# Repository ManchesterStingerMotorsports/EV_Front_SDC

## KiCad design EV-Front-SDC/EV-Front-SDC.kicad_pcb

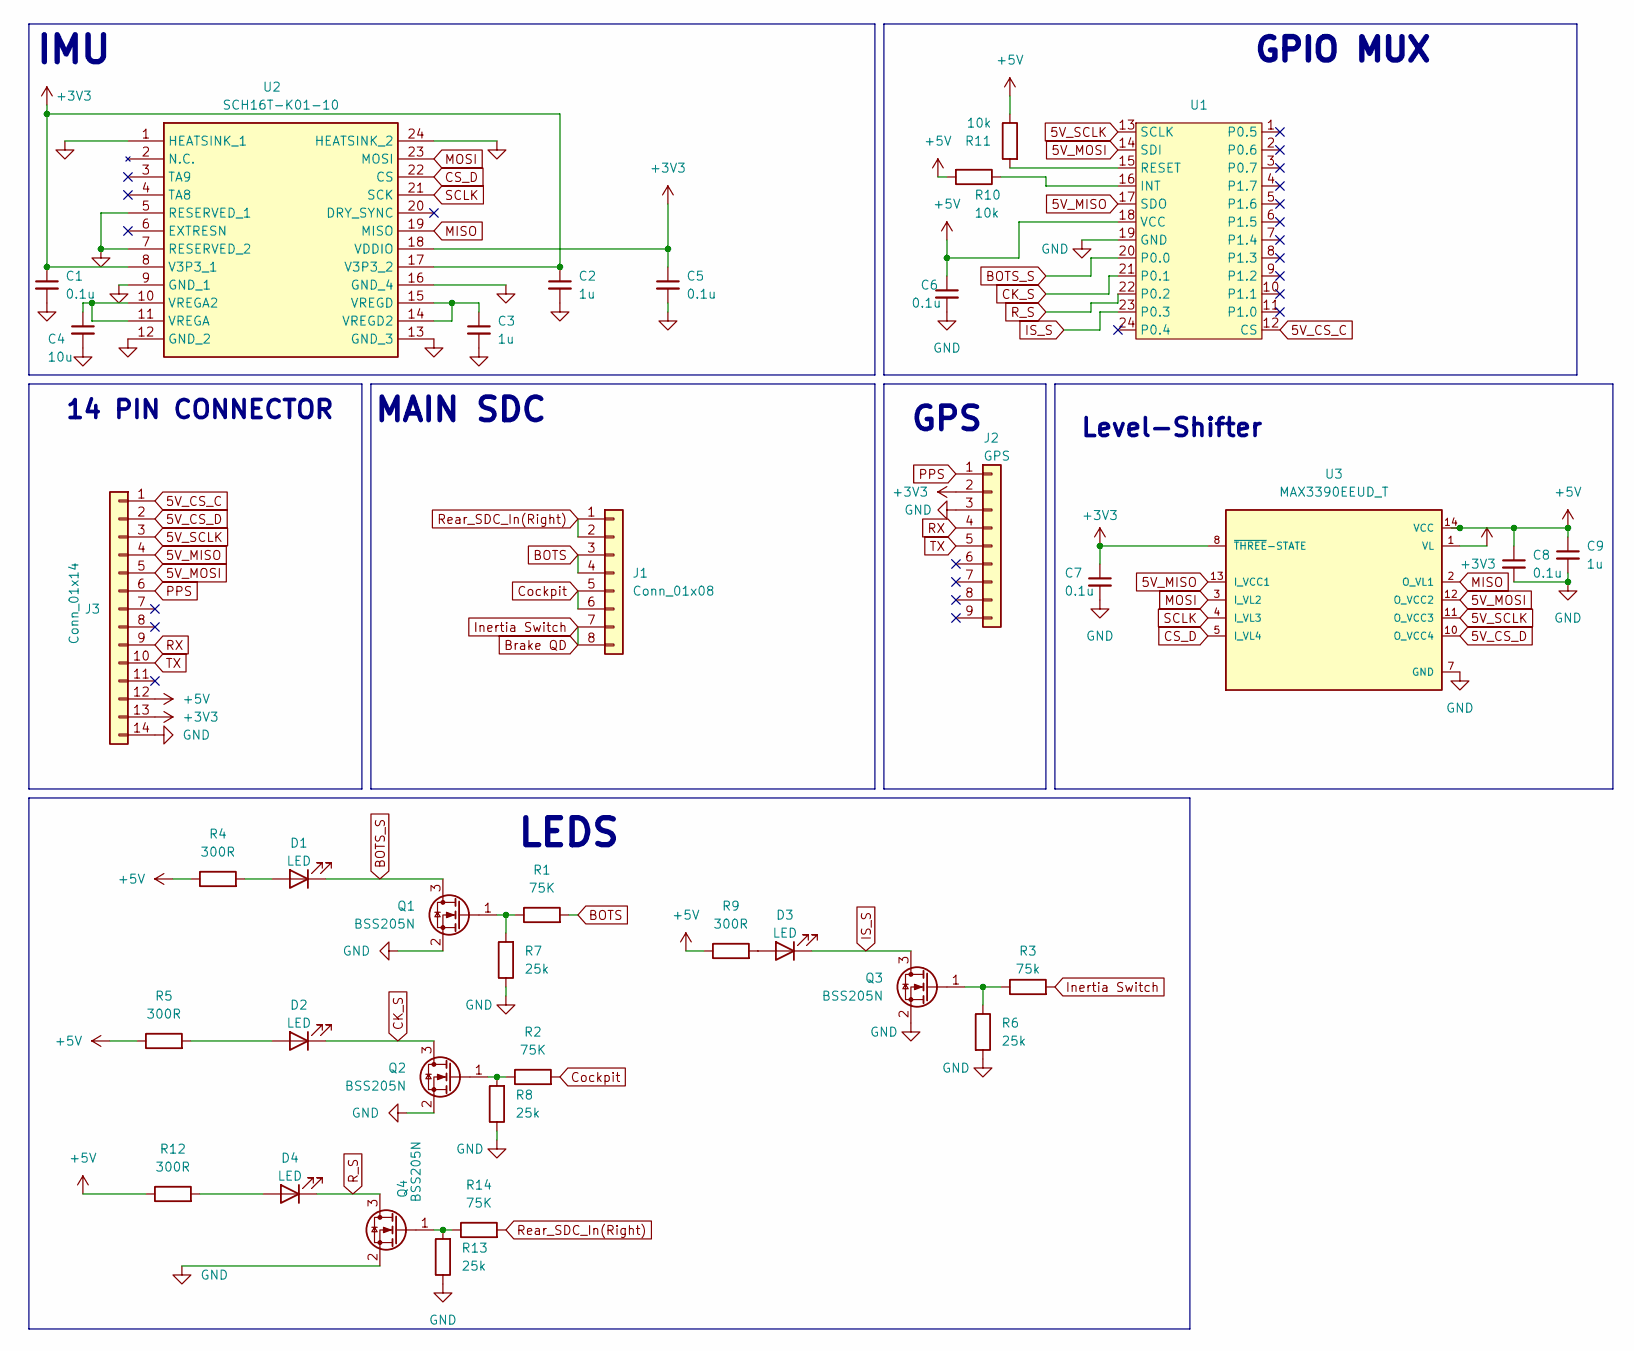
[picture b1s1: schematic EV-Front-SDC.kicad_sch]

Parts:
C1, C5, C6, C7, C8: 0.1u; C_0805_2012Metric
C2, C3, C9: 1u; C_0805_2012Metric
C4: 10u; C_0805_2012Metric
D1, D2, D3, D4: LED; LED_0805_2012Metric
J1: Conn_01x08; JST_XA_S08B-XASK-1_1x08_P2.50mm_Horizontal
J2: GPS
J3: Conn_01x14; JST_XA_S14B-XASK-1_1x14_P2.50mm_Horizontal
Q1, Q2, Q3, Q4: BSS205N; MOSFET_Single_SOT-23
R1, R2, R14: 75K; R_0805_2012Metric
R3: 75k; R_0805_2012Metric
R4, R5, R9, R12: 300R; R_0805_2012Metric
R6, R7, R8, R13: 25k; R_0805_2012Metric
R10, R11: 10k; R_0805_2012Metric
U1: QFN-24-1EP_4x4mm_P0.5mm_EP2.7x2.7mm
U2: SCH16T-K01-10; SCH16TK0110; Manufacturer_Part_Number SCH16T-K01-10
U3: MAX3390EEUD_T; TSSOP-14_4.4x5mm_P0.65mm

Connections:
5V_CS_C: J3.1, U1.12 (CS)
5V_CS_D: J3.2, U3.10 (O_VCC4)
5V_MISO: J3.4, U1.17 (SDO), U3.13 (I_VCC1)
5V_MOSI: J3.5, U1.14 (SDI), U3.12 (O_VCC2)
5V_SCLK: J3.3, U1.13 (SCLK), U3.11 (O_VCC3)
+3V3: C1.1, C2.1, C5.1, C7.1, J2.2, J3.13, U2.8 (V3P3_1), U2.17 (V3P3_2), U2.18 (VDDIO), U3.1 (VL), U3.8 (~THREE-STATE)
+5V: C6.1, C8.1, C9.1, J3.12, R4.1, R5.1, R9.1, R10.2, R11.1, R12.1, U1.18 (VCC), U3.14 (VCC)
BOTS: J1.3, J1.4, R1.2
BOTS_S: D1.1 (K), Q1.3 (D), U1.20 (P0.0)
Brake QD: J1.7, J1.8, R3.2
CK_S: D2.1 (K), Q2.3 (D), U1.21 (P0.1)
CS_D: U2.22 (CS), U3.5 (I_VL4)
Cockpit: J1.5, J1.6, R2.2
GND: C1.2, C2.2, C3.2, C4.2, C5.2, C6.2, C7.2, C8.2, C9.2, J2.3, J3.14, Q1.2 (S), Q2.2 (S), Q3.2 (S), Q4.2 (S), R6.2, R7.1, R8.1, R13.1, U1.19 (GND), U2.1 (HEATSINK_1), U2.5 (RESERVED_1), U2.7 (RESERVED_2), U2.9 (GND_1), U2.12 (GND_2), U2.13 (GND_3), U2.16 (GND_4), U2.24 (HEATSINK_2), U3.7 (GND)
IS_S: D3.1 (K), Q3.3 (D), U1.23 (P0.3)
MISO: U2.19 (MISO), U3.2 (O_VL1)
MOSI: U2.23 (MOSI), U3.3 (I_VL2)
unnamed: D1.2 (A), R4.2
unnamed: D2.2 (A), R5.2
unnamed: D3.2 (A), R9.2
unnamed: D4.2 (A), R12.2
unnamed: Q1.1 (G), R1.1, R7.2
unnamed: Q2.1 (G), R2.1, R8.2
unnamed: Q3.1 (G), R3.1, R6.1
unnamed: Q4.1 (G), R13.2, R14.1
unnamed: R10.1, U1.16 (INT)
unnamed: R11.2, U1.15 (RESET)
unnamed: C4.1, U2.10 (VREGA2), U2.11 (VREGA)
unnamed: C3.1, U2.14 (VREGD2), U2.15 (VREGD)
PPS: J2.1, J3.6
RX: J2.4, J3.9
R_S: D4.1 (K), Q4.3 (D), U1.22 (P0.2)
Rear_SDC_In(Right): J1.1, J1.2, R14.2
SCLK: U2.21 (SCK), U3.4 (I_VL3)
TX: J2.5, J3.10

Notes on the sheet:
LEDS
14 PIN CONNECTOR
Level-Shifter
IMU
GPIO MUX
MAIN SDC
GPS

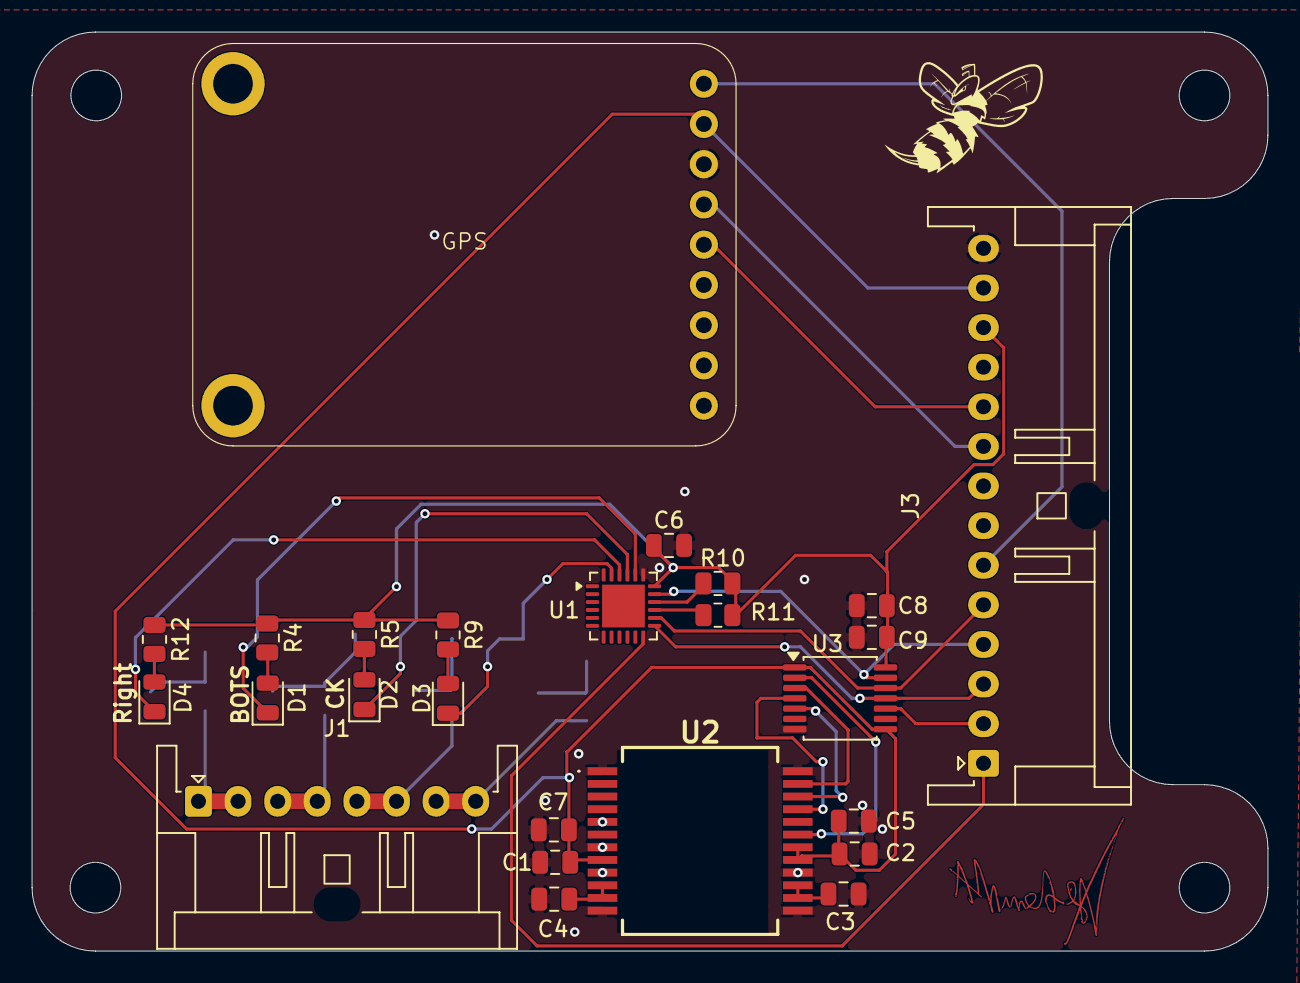
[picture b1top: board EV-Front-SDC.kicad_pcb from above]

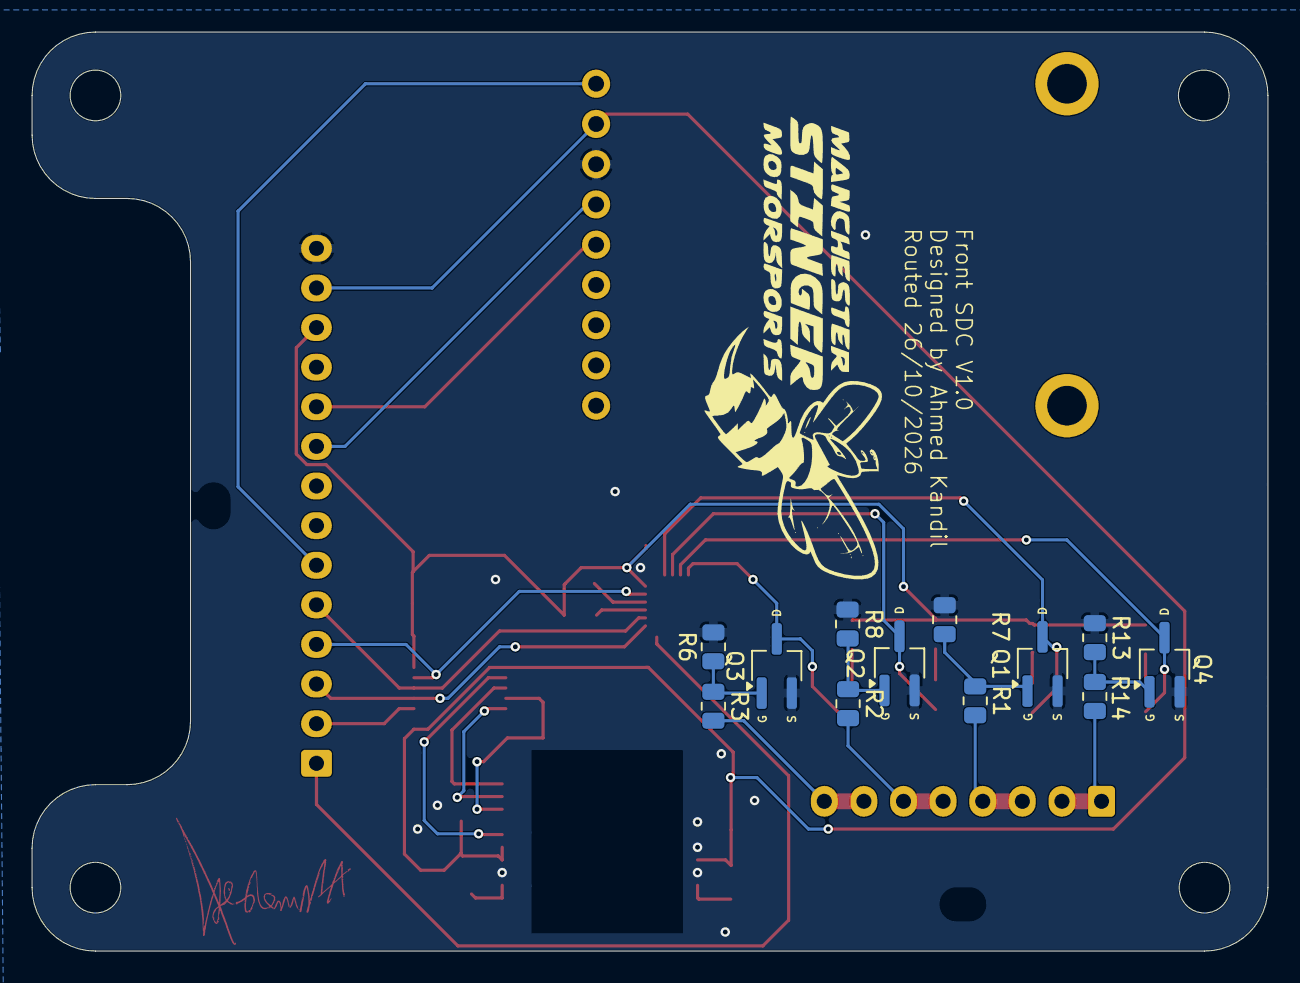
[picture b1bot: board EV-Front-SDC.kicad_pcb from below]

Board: 2 copper layers, 78.0 x 58.0 mm, 37 parts (12 on the bottom side), 35 nets.
